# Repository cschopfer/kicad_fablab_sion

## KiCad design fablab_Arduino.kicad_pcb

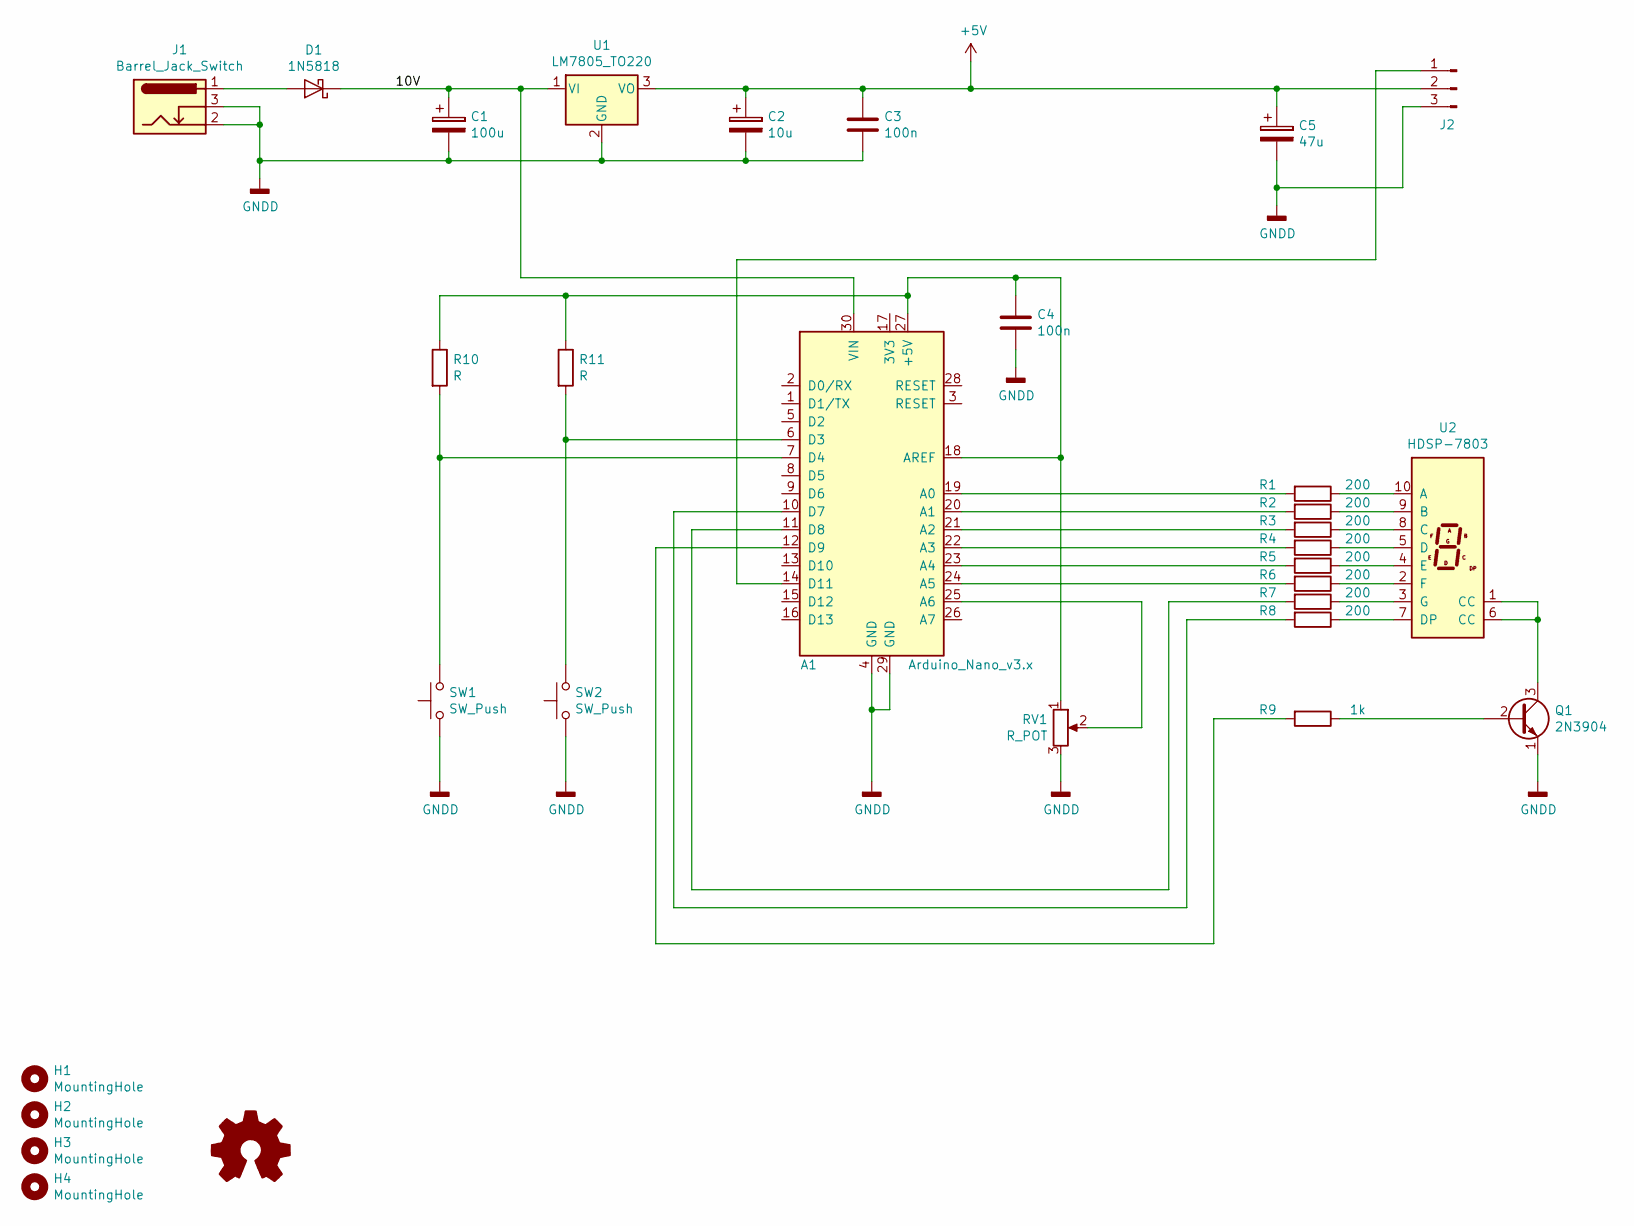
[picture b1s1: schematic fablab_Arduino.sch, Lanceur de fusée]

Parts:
A1: Arduino_Nano_v3.x; Arduino_Nano
C1: 100u; CP_Radial_D6.3mm_P2.50mm
C2: 10u; CP_Radial_D5.0mm_P2.00mm
C3, C4: 100n; C_Rect_L4.6mm_W3.0mm_P2.50mm_MKS02_FKP02
C5: 47u; CP_Radial_D5.0mm_P2.00mm
D1: 1N5818; D_DO-41_SOD81_P10.16mm_Horizontal
H1, H2, H3, H4: MountingHole; MountingHole_2.5mm
J1: Barrel_Jack_Switch; BarrelJack_Horizontal
J2: Conn_01x03_Male; PinHeader_1x03_P2.54mm_Vertical
Q1: 2N3904; TO-92_Inline
R1, R2, R3, R4, R5, R6, R7, R8: 200; R_Axial_DIN0204_L3.6mm_D1.6mm_P7.62mm_Horizontal
R9: 1k; R_Axial_DIN0204_L3.6mm_D1.6mm_P7.62mm_Horizontal
R10, R11: R; R_Axial_DIN0204_L3.6mm_D1.6mm_P7.62mm_Horizontal
RV1: R_POT; Potentiometer_Bourns_3266W_Vertical
SW1, SW2: SW_Push; SW_PUSH_6mm
U1: LM7805_TO220; TO-220-3_Vertical
U2: HDSP-7803; HDSP-7801

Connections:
+5V: C2.1, C3.1, C5.1, J2.2, U1.3 (VO)
/10V: A1.30 (VIN), C1.1, D1.1 (K), U1.1 (VI)
GNDD: A1.4 (GND), A1.29 (GND), C1.2, C2.2, C3.2, C4.2, C5.2, J1.2, J1.3, J2.3, Q1.1 (E), RV1.3, SW1.1, SW2.1, U1.2 (GND)
unnamed: A1.6 (D3), R11.2, SW2.2
unnamed: A1.7 (D4), R10.2, SW1.2
unnamed: A1.10 (D7), R8.2
unnamed: A1.11 (D8), R7.2
unnamed: A1.12 (D9), R9.2
unnamed: A1.14 (D11), J2.1
unnamed: A1.18 (AREF), A1.27 (+5V), C4.1, R10.1, R11.1, RV1.1
unnamed: A1.19 (A0), R1.2
unnamed: A1.20 (A1), R2.2
unnamed: A1.21 (A2), R3.2
unnamed: A1.22 (A3), R4.2
unnamed: A1.23 (A4), R5.2
unnamed: A1.24 (A5), R6.2
unnamed: A1.25 (A6), RV1.2
unnamed: D1.2 (A), J1.1
unnamed: Q1.2 (B), R9.1
unnamed: Q1.3 (C), U2.1 (CC), U2.6 (CC)
unnamed: R1.1, U2.10 (A)
unnamed: R2.1, U2.9 (B)
unnamed: R3.1, U2.8 (C)
unnamed: R4.1, U2.5 (D)
unnamed: R5.1, U2.4 (E)
unnamed: R6.1, U2.2 (F)
unnamed: R7.1, U2.3 (G)
unnamed: R8.1, U2.7 (DP)

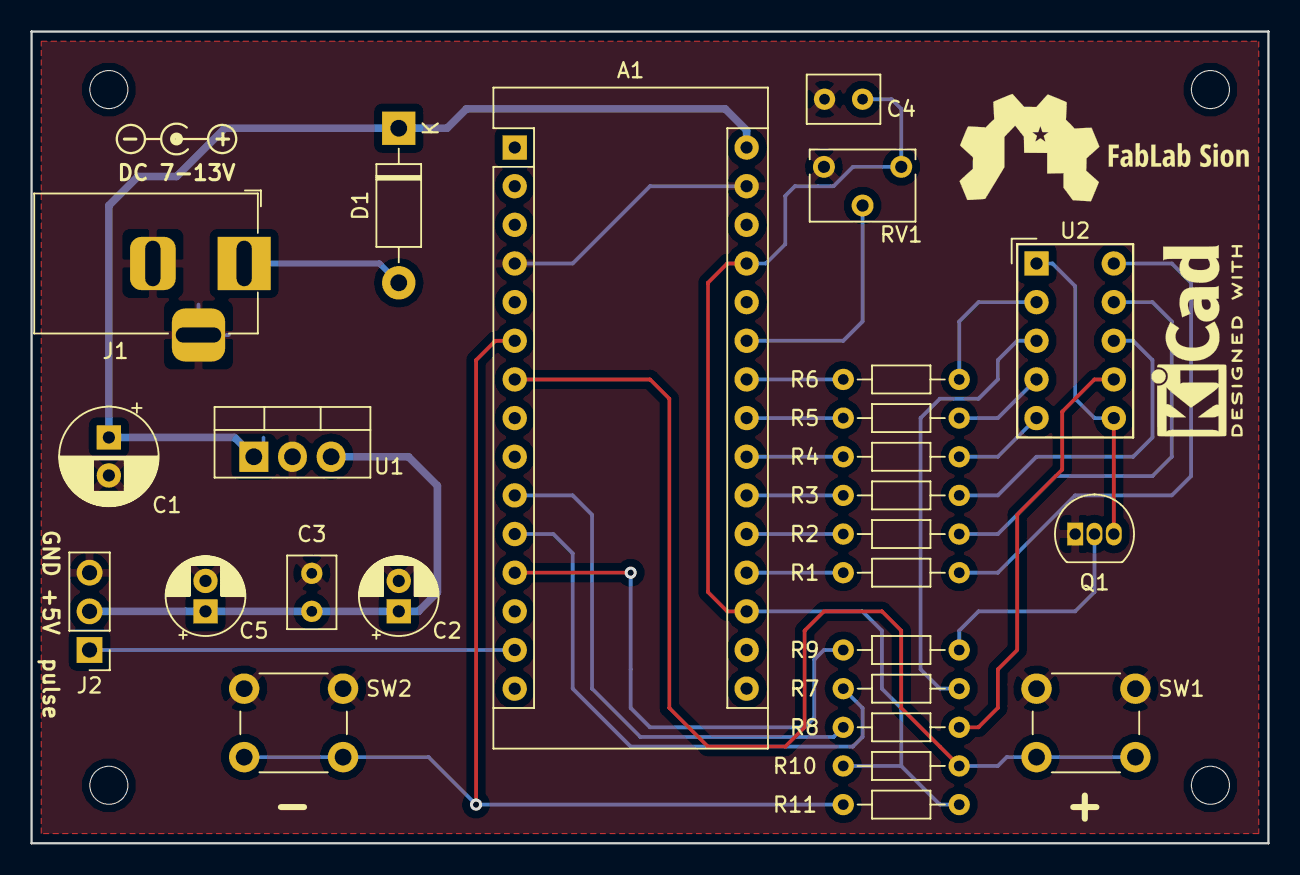
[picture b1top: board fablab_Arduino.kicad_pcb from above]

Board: 2 copper layers, 81.3 x 53.3 mm, 30 parts (0 on the bottom side), 28 nets.
